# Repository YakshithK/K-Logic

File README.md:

# K‑Logic Devboard

K‑Logic is a devboard I designed by following the Stasis starter devboard guide. my first PCB that goes! [stasis.hackclub](https://stasis.hackclub.com)

## What this is

- USB‑C powered devboard built with an RP2040
- Designed using the Stasis starter project flow (schematic → layout → silkscreen → fabrication)

## How to use it

- Plug it in over USB‑C.  
- Flash your firmware onto the main microcontroller.  
- Use the headers to hook up whatever logic / stuff you want.

## Why I built it

I've always wanted to get into hardware tech in general and I knew PCBs were going to be my first project in hardware after I found out about Stasis.

## Project structure

- `Journal/` – build log entries for each step (schematic, layout, silkscreen, fabrication, etc.). [github](https://github.com/YakshithK/K-Logic)
- `prod/` – production ZIP I sent to JLCPCB (gerbers + fab files). [github](https://github.com/YakshithK/K-Logic)
- `prod-files/` – BOM, CPL, and other manufacturing‑related files. [github](https://github.com/YakshithK/K-Logic)
- `DRC.rpt` – final DRC report from KiCad. [github](https://github.com/YakshithK/K-Logic)

## Screenshots

I have a bunch of screenshots of:

- Schematic in KiCad  
- PCB layout & 3D view  
- Silkscreen art and labels  
- JLCPCB upload / PCBA screens  

Check the `Screenshots/` dir

## BOM (short version)

Full BOM with links is in `K-Logic-Devboard-BOM-JLCPCB_Assembly_Order.csv` and `prod-files/`

| Part            | Value      | Notes                          |
| --------------- | ---------- | ------------------------------ |
| MCU             | (see BOM)  | Main brain of the board        |
| Flash memory    | W25Q16JVUXIQ | External flash for storage   |
| USB‑C connector | —          | Power + data input             |
| LDO regulator   | —          | Regulates USB power            |
| Passives        | various    | Resistors, caps, etc.          |

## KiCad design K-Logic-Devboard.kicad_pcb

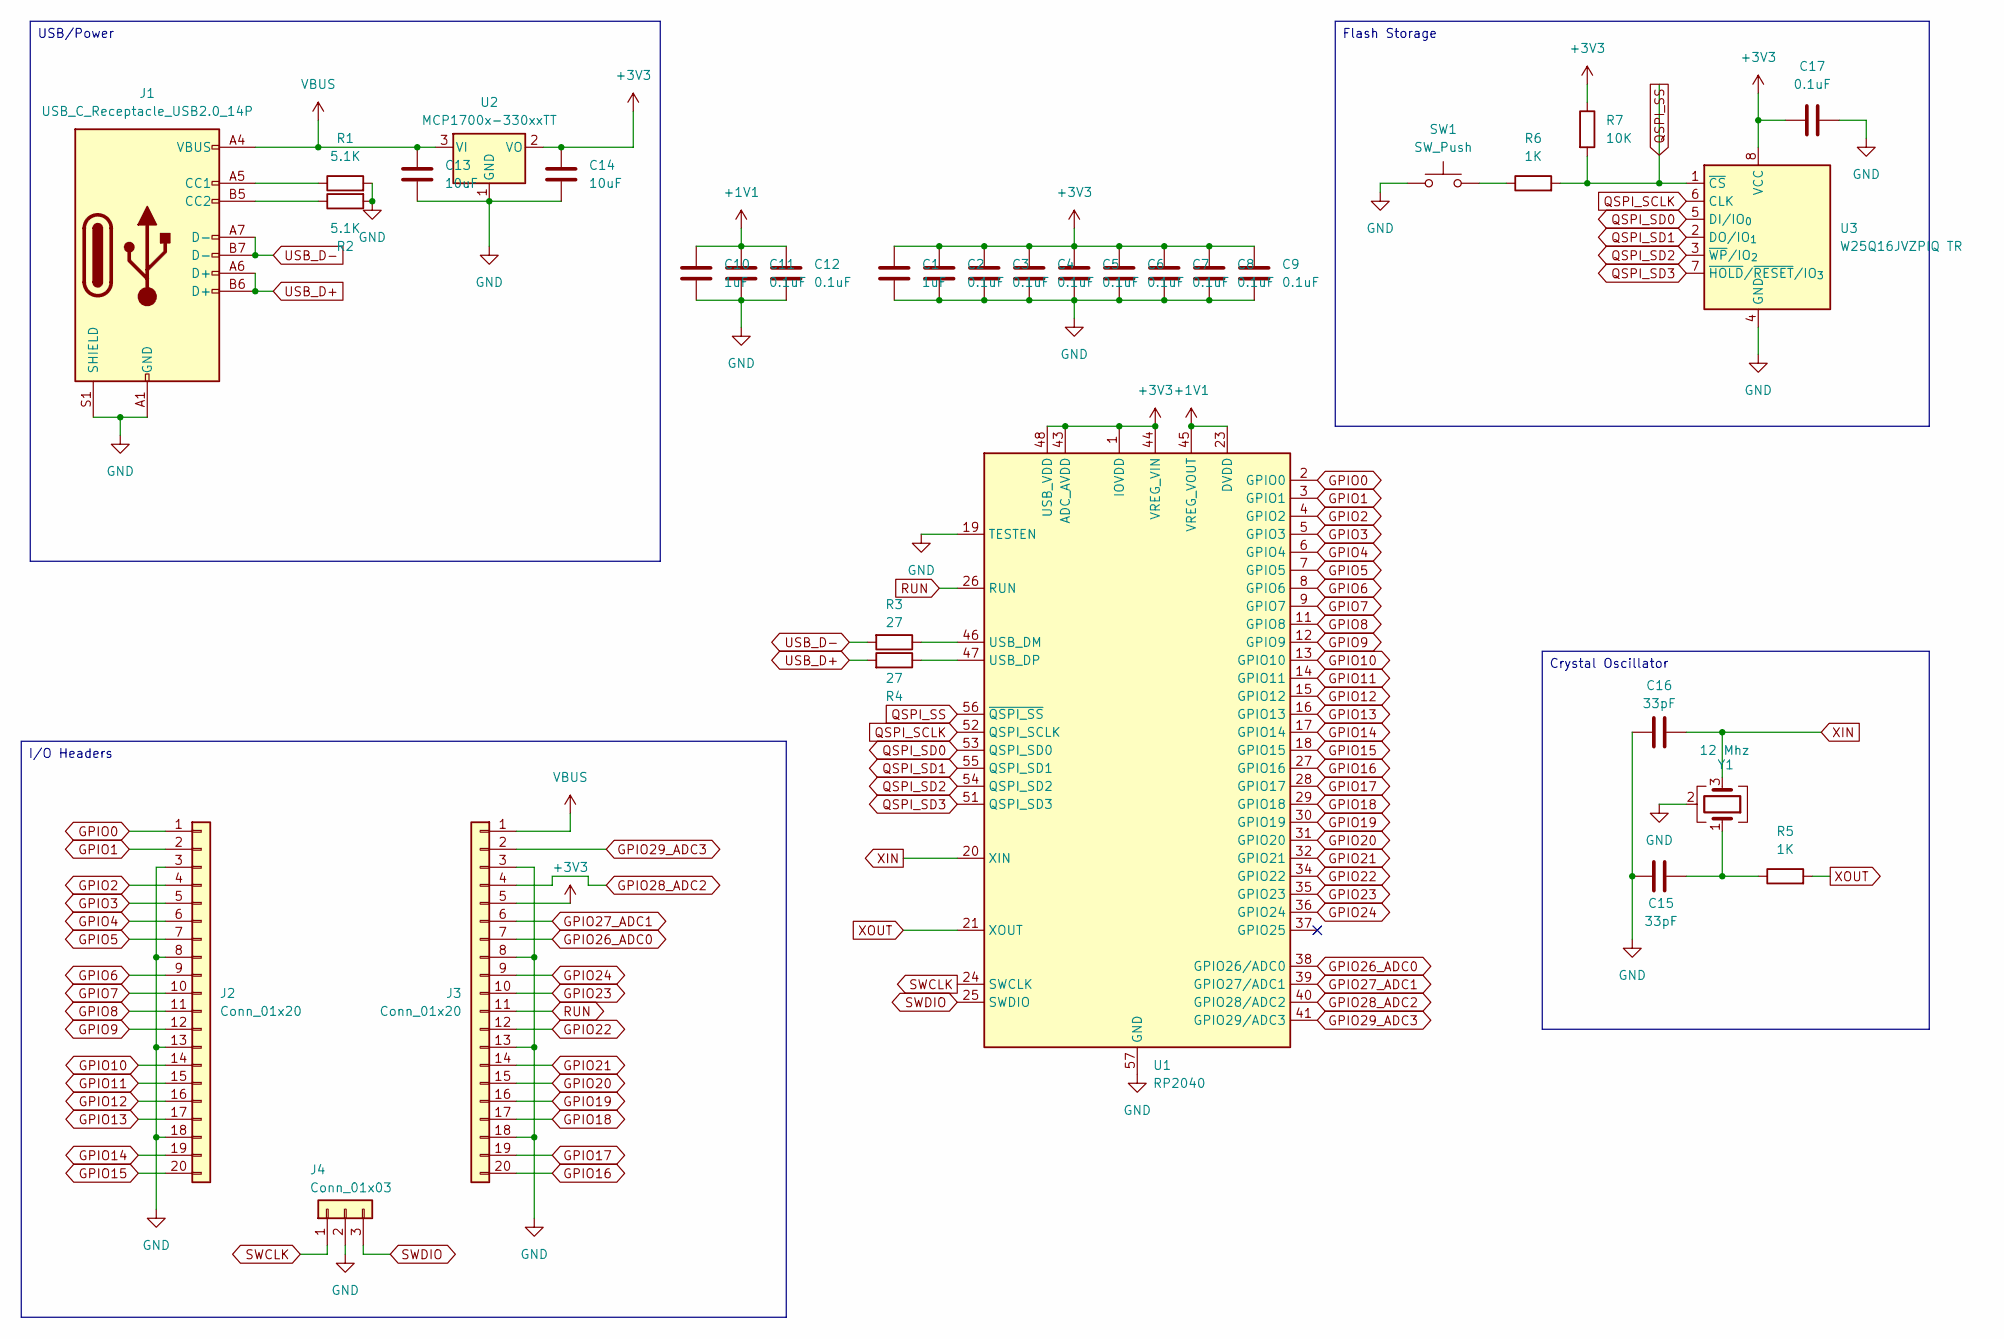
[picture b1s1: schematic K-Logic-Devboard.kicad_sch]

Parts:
C1, C10: 1uF; C_0402_1005Metric
C2, C3, C4, C5, C6, C7, C8, C9, C11, C12, C17: 0.1uF; C_0402_1005Metric
C13, C14: 10uF; C_0603_1608Metric
C15, C16: 33pF; C_0402_1005Metric
J1: USB_C_Receptacle_USB2.0_14P; USB_C_Receptacle_HRO_TYPE-C-31-M-12
J2, J3: Conn_01x20; PinHeader_1x20_P2.54mm_Vertical
J4: Conn_01x03; PinHeader_1x03_P2.54mm_Vertical
R1, R2: 5.1K; R_0402_1005Metric
R3, R4: 27; R_0402_1005Metric
R5, R6: 1K; R_0402_1005Metric
R7: 10K; R_0402_1005Metric
SW1: SW_Push; SW_Push_SPST_NO_Alps_SKRK
U1: RP2040; QFN-56-1EP_7x7mm_P0.4mm_EP3.2x3.2mm
U2: MCP1700x-330xxTT; SOT-23-3
U3: W25Q16JVZPIQ TR; Winbond_USON-8-1EP_3x2mm_P0.5mm_EP0.2x1.6mm
Y1: 12 Mhz; Crystal_SMD_3225-4Pin_3.2x2.5mm

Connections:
+1V1: C10.1, C11.1, C12.1, U1.23 (DVDD), U1.45 (VREG_VOUT), U1.50 (DVDD)
+3V3: C1.1, C2.1, C3.1, C4.1, C5.1, C6.1, C7.1, C8.1, C9.1, C14.1, C17.2, J3.5, R7.1, U1.1 (IOVDD), U1.10 (IOVDD), U1.22 (IOVDD), U1.33 (IOVDD), U1.42 (IOVDD), U1.43 (ADC_AVDD), U1.44 (VREG_VIN), U1.48 (USB_VDD), U1.49 (IOVDD), U2.2 (VO), U3.8 (VCC)
GND: C1.2, C2.2, C3.2, C4.2, C5.2, C6.2, C7.2, C8.2, C9.2, C10.2, C11.2, C12.2, C13.2, C14.2, C15.2, C16.2, C17.1, J1.A1 (GND), J1.A12 (GND), J1.B1 (GND), J1.B12 (GND), J1.S1 (SHIELD), J2.3, J2.8, J2.13, J2.18, J3.3, J3.8, J3.13, J3.18, J4.2, R1.2, R2.2, SW1.1, U1.19 (TESTEN), U1.57 (GND), U2.1 (GND), U3.4 (GND), Y1.2 (G), Y1.4 (G)
GPIO0: J2.1, U1.2 (GPIO0)
GPIO1: J2.2, U1.3 (GPIO1)
GPIO2: J2.4, U1.4 (GPIO2)
GPIO3: J2.5, U1.5 (GPIO3)
GPIO4: J2.6, U1.6 (GPIO4)
GPIO5: J2.7, U1.7 (GPIO5)
GPIO6: J2.9, U1.8 (GPIO6)
GPIO7: J2.10, U1.9 (GPIO7)
GPIO8: J2.11, U1.11 (GPIO8)
GPIO9: J2.12, U1.12 (GPIO9)
GPIO10: J2.14, U1.13 (GPIO10)
GPIO11: J2.15, U1.14 (GPIO11)
GPIO12: J2.16, U1.15 (GPIO12)
GPIO13: J2.17, U1.16 (GPIO13)
GPIO14: J2.19, U1.17 (GPIO14)
GPIO15: J2.20, U1.18 (GPIO15)
GPIO16: J3.20, U1.27 (GPIO16)
GPIO17: J3.19, U1.28 (GPIO17)
GPIO18: J3.17, U1.29 (GPIO18)
GPIO19: J3.16, U1.30 (GPIO19)
GPIO20: J3.15, U1.31 (GPIO20)
GPIO21: J3.14, U1.32 (GPIO21)
GPIO22: J3.12, U1.34 (GPIO22)
GPIO23: J3.10, U1.35 (GPIO23)
GPIO24: J3.9, U1.36 (GPIO24)
GPIO26_ADC0: J3.7, U1.38 (GPIO26/ADC0)
GPIO27_ADC1: J3.6, U1.39 (GPIO27/ADC1)
GPIO28_ADC2: J3.4, U1.40 (GPIO28/ADC2)
GPIO29_ADC3: J3.2, U1.41 (GPIO29/ADC3)
unnamed: C15.1, R5.1, Y1.1
unnamed: J1.A5 (CC1), R1.1
unnamed: J1.B5 (CC2), R2.1
unnamed: R6.1, SW1.2
unnamed: R3.1, U1.46 (USB_DM)
unnamed: R4.1, U1.47 (USB_DP)
QSPI_SCLK: U1.52 (QSPI_SCLK), U3.6 (CLK)
QSPI_SD0: U1.53 (QSPI_SD0), U3.5 (DI/IO_{0})
QSPI_SD1: U1.55 (QSPI_SD1), U3.2 (DO/IO_{1})
QSPI_SD2: U1.54 (QSPI_SD2), U3.3 (~WP/IO_{2})
QSPI_SD3: U1.51 (QSPI_SD3), U3.7 (~HOLD/~RESET/IO_{3})
QSPI_SS: R6.2, R7.2, U1.56 (~QSPI_SS), U3.1 (~CS)
RUN: J3.11, U1.26 (RUN)
SWCLK: J4.1, U1.24 (SWCLK)
SWDIO: J4.3, U1.25 (SWDIO)
USB_D+: J1.A6 (D+), J1.B6 (D+), R4.2
USB_D-: J1.A7 (D-), J1.B7 (D-), R3.2
VBUS: C13.1, J1.A4 (VBUS), J1.A9 (VBUS), J1.B4 (VBUS), J1.B9 (VBUS), J3.1, U2.3 (VI)
XIN: C16.1, U1.20 (XIN), Y1.3
XOUT: R5.2, U1.21 (XOUT)

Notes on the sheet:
Crystal Oscillator
I/O Headers
USB/Power
Flash Storage

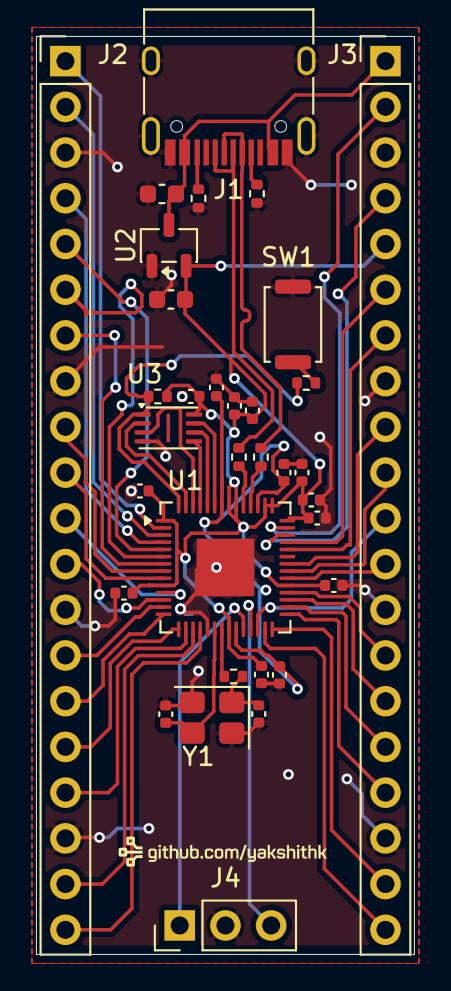
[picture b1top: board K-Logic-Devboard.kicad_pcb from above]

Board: 2 copper layers, 21.0 x 51.0 mm, 33 parts (0 on the bottom side), 52 nets.

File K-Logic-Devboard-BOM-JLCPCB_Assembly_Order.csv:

Top Designator,Bottom Designator,Comment,Footprint,JLCPCB Part #,Matches,Part # ,Manufacturer,Footprint,Description,Category,Warning,JLCPCB Part #,Product link,Lib Type,Qty,Source,Total Price ($)
"C10,C1",,1uF,C_0402_1005Metric,,Select by Customer,CL05A105KA5NQNC,Samsung Electro-Mechanics,0402,1uF 25V X5R ±10% 0402 Multilayer Ceramic Capacitors MLCC - SMD/SMT ROHS,Multilayer Ceramic Capacitors MLCC - SMD/SMT,,C52923,https://jlcpcb.com/partdetail/53938-CL05A105KA5NQNC/C52923,Basic,20,20 JLCPCB,0.08
"C11,C5,C6,C2,C12,C9,C7,C17,C4,C8,C3",,0.1uF,C_0402_1005Metric,,Select by Customer,CL05B104KO5NNNC,Samsung Electro-Mechanics,0402,100nF 16V X7R ±10% 0402 Multilayer Ceramic Capacitors MLCC - SMD/SMT ROHS,Multilayer Ceramic Capacitors MLCC - SMD/SMT,1.The comment (CL05B104KO5NNNC) of this part does not match the one (0.1uF) provided in your BOM. Please confirm;,C1525,https://jlcpcb.com/partdetail/1877-CL05B104KO5NNNC/C1525,Basic,65,65 JLCPCB,0.0845
"C14,C13",,10uF,C_0603_1608Metric,,Select by Customer,CL10A106KP8NNNC,Samsung Electro-Mechanics,0603,10V 10uF X5R ±10% 0603 Multilayer Ceramic Capacitors MLCC - SMD/SMT ROHS,Multilayer Ceramic Capacitors MLCC - SMD/SMT,,C19702,https://jlcpcb.com/partdetail/20411-CL10A106KP8NNNC/C19702,Basic,20,20 JLCPCB,0.144
"C16,C15",,33pF,C_0402_1005Metric,,Select by Customer,0402CG330J500NT,FH (Guangdong Fenghua Advanced Tech),0402,33pF 50V C0G ±5% 0402 Multilayer Ceramic Capacitors MLCC - SMD/SMT ROHS,Multilayer Ceramic Capacitors MLCC - SMD/SMT,,C1562,https://jlcpcb.com/partdetail/1914-0402CG330J500NT/C1562,Basic,20,20 JLCPCB,0.024
J1,,USB_C_Receptacle_USB2.0_14P,USB_C_Receptacle_HRO_TYPE-C-31-M-12,,Select by Customer,TYPE-C-31-M-12,Korean Hroparts Elec,SMD,"-30℃~+80℃ 1 10,000 cycles 16P 20V 5A 7.35mm Female Surface Mount, Right Angle Type-C SMD USB Connectors ROHS",USB Connectors,,C165948,https://jlcpcb.com/partdetail/Korean_HropartsElec-TYPE_C_31_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,Extended,5,5 JLCPCB,0.906
"J3,J2",,Conn_01x20,PinHeader_1x20_P2.54mm_Vertical,,Select by Customer,2.54-1*20P直针,BOOMELE(Boom Precision Elec),"插件,P=2.54mm","-40℃~+105℃ 1 1x20P 2.54mm 20P 3A Black Brass Pin Header Through Hole Plugin,P=2.54mm Pin Headers ROHS",Pin Headers,,C50981,https://jlcpcb.com/partdetail/51993-2_54_1_20P/C50981,Extended,0,0 JLCPCB,0
J4,,Conn_01x03,PinHeader_1x03_P2.54mm_Vertical,,Select by Customer,1.27-1*3P针,BOOMELE(Boom Precision Elec),"插件,P=1.27mm","-55℃~+105℃ 1 1.27mm 1.7mm 1x3P 2.5mm 3A 3P 3mm Black Brass Pin Header Through Hole Plugin,P=1.27mm Pin Headers ROHS",Pin Headers,,C24980,https://jlcpcb.com/partdetail/25717-1_27_1_3P/C24980,Extended,0,0 JLCPCB,0
"R2,R1",,5.1K,R_0402_1005Metric,,Select by Customer,0402WGF5101TCE,UNI-ROYAL(Uniroyal Elec),0402,-55℃~+155℃ 5.1kΩ 50V 62.5mW Thick Film Resistor ±1% ±100ppm/℃ 0402 Chip Resistor - Surface Mount ROHS,Chip Resistor - Surface Mount,,C25905,https://jlcpcb.com/partdetail/26648-0402WGF5101TCE/C25905,Basic,20,20 JLCPCB,0.016
"R4,R3",,27,R_0402_1005Metric,,Select by Customer,0402WGF270JTCE,UNI-ROYAL(Uniroyal Elec),0402,-55℃~+155℃ 27Ω 50V 62.5mW Thick Film Resistor ±1% ±100ppm/℃ 0402 Chip Resistor - Surface Mount ROHS,Chip Resistor - Surface Mount,1.The comment (0402WGF270JTCE) of this part does not match the one (27) provided in your BOM. Please confirm;,C25100,https://jlcpcb.com/partdetail/25843-0402WGF270JTCE/C25100,Extended,22,22 JLCPCB,0.0176
"R5,R6",,1K,R_0402_1005Metric,,Select by Customer,0402WGF1001TCE,UNI-ROYAL(Uniroyal Elec),0402,-55℃~+155℃ 1kΩ 50V 62.5mW Thick Film Resistor ±1% ±100ppm/℃ 0402 Chip Resistor - Surface Mount ROHS,Chip Resistor - Surface Mount,1.The comment (0402WGF1001TCE) of this part does not match the one (1K) provided in your BOM. Please confirm;,C11702,https://jlcpcb.com/partdetail/12256-0402WGF1001TCE/C11702,Basic,20,20 JLCPCB,0.014
R7,,10K,R_0402_1005Metric,,Select by Customer,0402WGF1002TCE,UNI-ROYAL(Uniroyal Elec),0402,-55℃~+155℃ 10kΩ 50V 62.5mW Thick Film Resistor ±1% ±100ppm/℃ 0402 Chip Resistor - Surface Mount ROHS,Chip Resistor - Surface Mount,1.The comment (0402WGF1002TCE) of this part does not match the one (10K) provided in your BOM. Please confirm;,C25744,https://jlcpcb.com/partdetail/26487-0402WGF1002TCE/C25744,Basic,20,20 JLCPCB,0.016
SW1,,SW_Push,SW_Push_SPST_NO_Alps_SKRK,,Select by Customer,TS-1088-AR02016,XUNPU,"SMD,4x3mm","-30℃~+80℃ 1.6N 100,000 cycles 12V 2mm 3mm 4mm 50mA Black Round Button SMD(SMT) Tab SPST Surface Mount,Vertical Without Bracket SMD,4x3mm Tactile Switches ROHS",Tactile Switches,,C720477,https://jlcpcb.com/partdetail/XUNPU-TS_1088AR02016/C720477,Basic,9,9 JLCPCB,0.4815
U1,,RP2040,QFN-56-1EP_7x7mm_P0.4mm_EP3.2x3.2mm,,Select by Customer,RP2040,Raspberry Pi,LQFN-56(7x7),12bit 133MHz 30 LQFN-56(7x7) Microcontrollers (MCU/MPU/SOC) ROHS,Microcontrollers (MCU/MPU/SOC),,C2040,https://jlcpcb.com/partdetail/RaspberryPi-RP2040/C2040,Extended,5,5 JLCPCB,4.8295
U2,,MCP1700x-330xxTT,SOT-23-3,,Select by Customer,MCP1700T-3302E/TT,Microchip Tech,SOT-23,"-40℃~+125℃@(Tj) 1 1.6uA 178mV@(250mA) 250mA 3.3V 44dB@(100Hz) 6V Fixed Over Temperature Protection、Short Circuit Protection Positive SOT-23 Voltage Regulators - Linear, Low Drop Out (LDO) Regulators ROHS","Voltage Regulators - Linear, Low Drop Out (LDO) Regulators",,C39051,https://jlcpcb.com/partdetail/MicrochipTech-MCP1700T_3302ETT/C39051,Extended,5,5 JLCPCB,1.864
U3,,W25Q16JVZPIQTR,Winbond_USON-8-1EP_3x2mm_P0.5mm_EP0.2x1.6mm,,Select by Customer,W25Q16JVUXIQ,Winbond Elec,USON-8-EP(2x3),"-40℃~+85℃ 100,000 cycles 10uA 133MHz 16Mbit 2.7V~3.6V 20 Years 3ms SPI USON-8-EP(2x3) NOR FLASH ROHS",NOR FLASH,1.The comment (W25Q16JVUXIQ) of this part does not match the one (W25Q16JVZPIQTR) provided in your BOM. Please confirm;,C2843335,https://jlcpcb.com/partdetail/WinbondElec-W25Q16JVUXIQ/C2843335,Extended,5,5 JLCPCB,8.331
Y1,,12Mhz,Crystal_SMD_3225-4Pin_3.2x2.5mm,,Select by Customer,X322512MSB4SI,YXC Crystal Oscillators,SMD3225-4P,-40℃~+85℃ 12MHz 20pF Crystal Oscillator ±10ppm ±20ppm SMD3225-4P Crystals ROHS,Crystals,,C9002,https://jlcpcb.com/partdetail/YXC_CrystalOscillators-X322512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,Basic,9,9 JLCPCB,0.6534

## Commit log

2026-03-10 worked on flash storage, i/o headers and footprints
2026-03-11 third session: worked on the pcb design
2026-03-11 Fix formatting and clean up first journal entry
    Corrected formatting and removed extra blank lines.
2026-03-11 Fix formatting in session2.md
    Updated the session notes to improve formatting and clarity.
2026-03-11 Fix formatting and remove duplicate images in session3.md
2026-03-22 pcb 99.99% done. journals and BOM.
2026-03-22 we done
2026-03-22 readme + screenshots
